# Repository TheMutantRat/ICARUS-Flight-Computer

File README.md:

# ICARUS-Flight-Computer
modular high-power rocketry flight computer

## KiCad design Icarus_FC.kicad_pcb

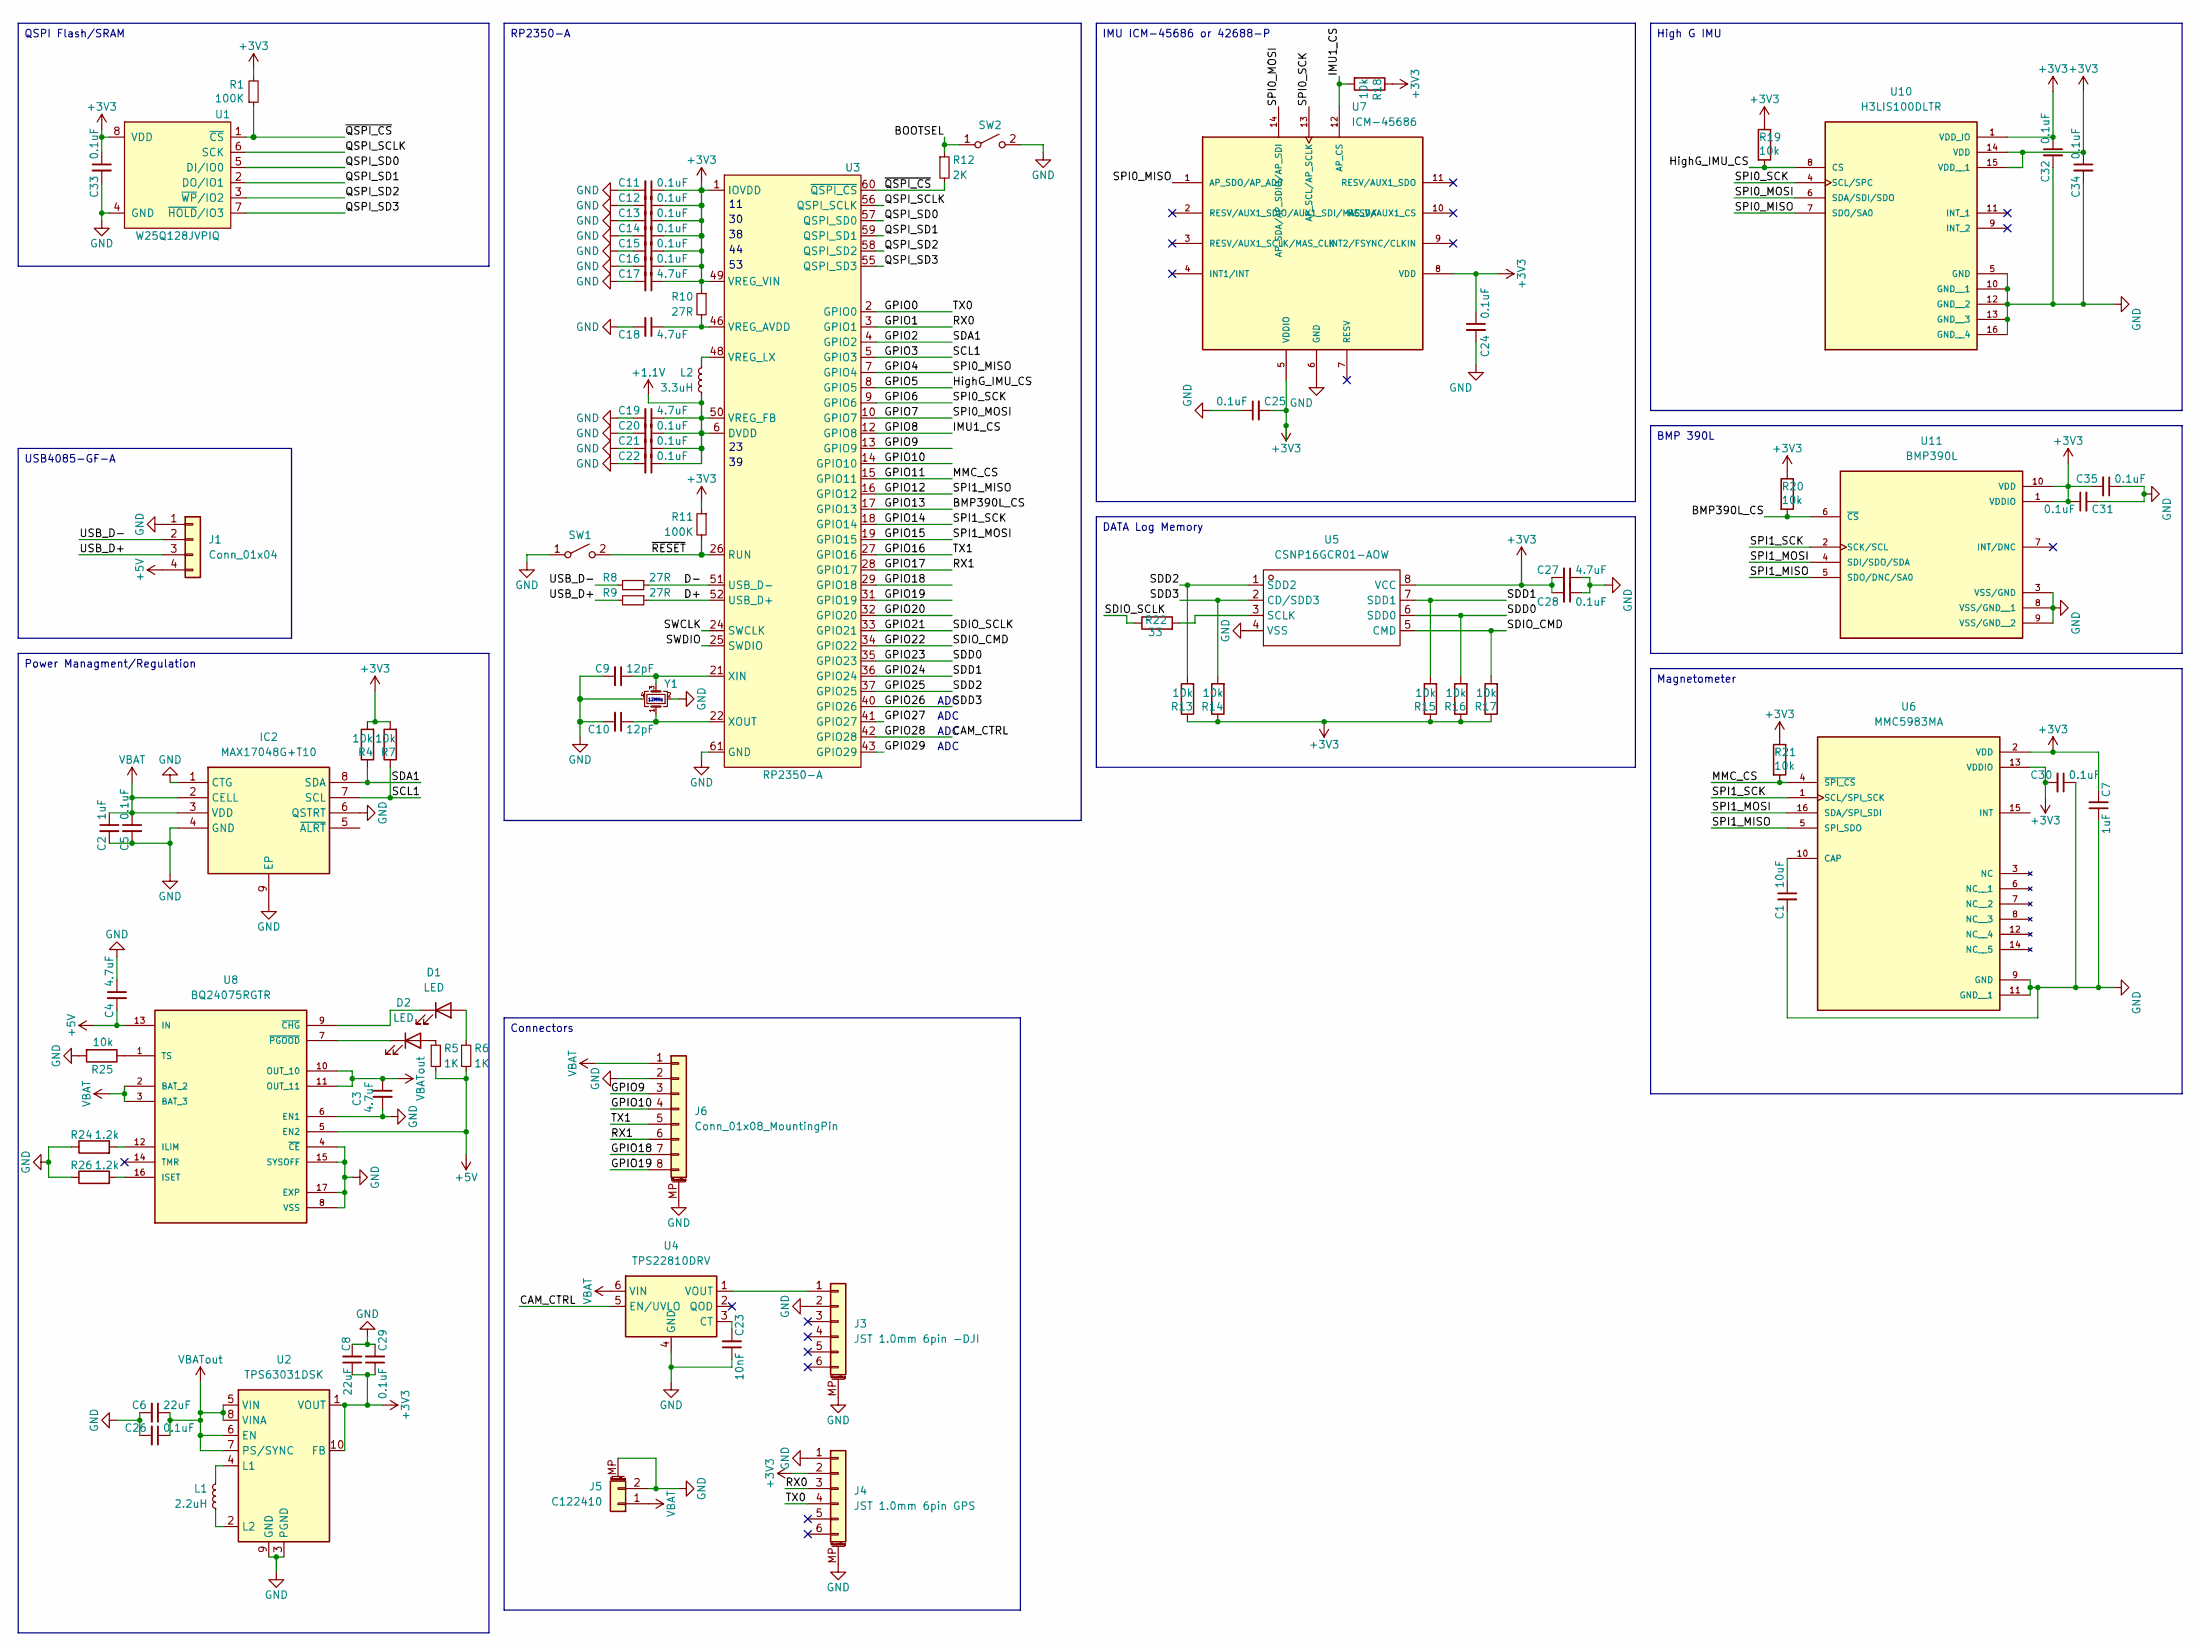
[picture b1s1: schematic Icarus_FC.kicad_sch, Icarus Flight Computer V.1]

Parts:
C1: 10uF; C_0402_1005Metric
C2, C7: 1uF; C_0201_0603Metric
C3, C4, C17, C18, C19, C27: 4.7uF; C_0201_0603Metric
C5, C11, C12, C13, C14, C15, C16, C20, C21, C22, C24, C25, C26, C28, C29, C30, C31, C32, C33, C34, C35: 0.1uF; C_0201_0603Metric
C6, C8: 22uF; C_0402_1005Metric
C9, C10: 12pF; C_0201_0603Metric
C23: 10nF; C_0201_0603Metric
D1, D2: LED; LED_0201_0603Metric
IC2: MAX17048G+T10; SON50P200X200X80-9N-D; Mouser Part Number 700-MAX17048G+T10
J1: Conn_01x04; JST_SH_SM04B-SRSS-TB_1x04-1MP_P1.00mm_Horizontal
J3: JST 1.0mm 6pin -DJI; JST_SH_SM06B-SRSS-TB_1x06-1MP_P1.00mm_Horizontal
J4: JST 1.0mm 6pin GPS; JST_SH_SM06B-SRSS-TB_1x06-1MP_P1.00mm_Horizontal
J5: C122410; Molex_PicoBlade_53398-0271_1x02-1MP_P1.25mm_Vertical
J6: Conn_01x08_MountingPin; JST_SH_SM08B-SRSS-TB_1x08-1MP_P1.00mm_Horizontal
L1: 2.2uH; ASMPM-0806; LCSC C17701149
L2: 3.3uH; ASMPM-0806; LCSC C42411119
R1, R11: 100K; R_0201_0603Metric
R4, R7, R13, R14, R15, R16, R17, R18, R19, R20, R21, R25: 10k; R_0201_0603Metric
R5, R6: 1K; R_0201_0603Metric
R8, R9, R10: 27R; R_0201_0603Metric
R12: 2K; R_0201_0603Metric
R22: 33; R_0201_0603Metric
R24, R26: 1.2k; R_0201_0603Metric
SW1: SW_BOOTSEL; KEY-SMD_B3U-3000P; LCSC C963349
SW2: SW_RESET; KEY-SMD_B3U-3000P; LCSC C963349
U1: W25Q128JVPIQ; WSON-8-1EP_6x5mm_P1.27mm_EP3.4x4mm; LCSC C190862
U2: TPS63031DSK; WSON-10-1EP_2.5x2.5mm_P0.5mm_EP1.2x2mm_ThermalVias
U3: RP2350-A; QFN-60-1EP_7x7mm_P0.4mm_EP3.4x3.4mm_ThermalVias
U4: TPS22810DRV; WSON-6-1EP_2x2mm_P0.65mm_EP1x1.6mm
U5: CSNP16GCR01-AOW; LGA-8_8x6.2mm_P1.27mm; Manufacturer Part CSNP16GCR01-AOW; LCSC Part Name CS Gen2 SDNAND 16Gb pSLC LongP/ECycle 工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
U6: MMC5983MA; PQFN50P300X300X100-16N; PARTREV A
U7: ICM-45686; IC_ICM-45686; PARTREV 0.2
U8: BQ24075RGTR; QFN50P300X300X100-17N; PARTREV M
U10: H3LIS100DLTR; PQFN50P300X300X100-16N; PARTREV 2
U11: BMP390L; 10LGA_2X2X0p75_BOS; PARTREV 1.7
Y1: CM4012M00012001; Crystal_SMD_2520-4Pin_2.5x2.0mm; LCSC C7294611

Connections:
+1.1V: C19.1, C20.1, C21.1, C22.1, L2.1, U3.6 (DVDD), U3.23 (DVDD), U3.39 (DVDD), U3.50 (VREG_FB)
+3V3: C7.2, C8.1, C11.1, C12.1, C13.1, C14.1, C15.1, C16.1, C17.1, C24.1, C25.2, C27.2, C28.2, C29.1, C30.2, C31.1, C32.1, C33.1, C34.1, C35.2, J4.2, R1.2, R4.2, R7.2, R10.1, R11.1, R13.1, R14.1, R15.1, R16.1, R17.1, R18.1, R19.1, R20.1, R21.1, U1.8 (VDD), U2.1 (VOUT), U2.10 (FB), U3.1 (IOVDD), U3.11 (IOVDD), U3.20 (IOVDD), U3.30 (IOVDD), U3.38 (IOVDD), U3.44 (IOVDD), U3.45 (IOVDD), U3.49 (VREG_VIN), U3.53 (IOVDD), U3.54 (IOVDD), U5.8 (VCC), U6.2 (VDD), U6.13 (VDDIO), U7.5 (VDDIO), U7.8 (VDD), U10.1 (VDD_IO), U10.14 (VDD), U10.15 (VDD__1), U11.1 (VDDIO), U11.10 (VDD)
+5V: C4.2, J1.4, R5.2, R6.2, U8.5 (EN2), U8.13 (IN)
/BMP390L_CS: R20.2, U3.17 (GPIO13), U11.6 (~CS)
/BOOTSEL: R12.1, SW2.1 (A)
/CAM_CTRL: U3.42 (GPIO28), U4.5 (EN/UVLO)
/D+: R9.1, U3.52 (USB_D+)
/D-: R8.1, U3.51 (USB_D-)
/GPIO0: J4.4, U3.2 (GPIO0)
/GPIO1: J4.3, U3.3 (GPIO1)
/GPIO2: IC2.8 (SDA), R4.1, U3.4 (GPIO2)
/GPIO3: IC2.7 (SCL), R7.1, U3.5 (GPIO3)
/GPIO4: U3.7 (GPIO4), U7.1 (AP_SDO/AP_AD0), U10.7 (SDO/SA0)
/GPIO5: R19.2, U3.8 (GPIO5), U10.8 (CS)
/GPIO6: U3.9 (GPIO6), U7.13 (AP_SCL/AP_SCLK), U10.4 (SCL/SPC)
/GPIO7: U3.10 (GPIO7), U7.14 (AP_SDA/AP_SDIO/AP_SDI), U10.6 (SDA/SDI/SDO)
/GPIO8: R18.2, U3.12 (GPIO8), U7.12 (AP_CS)
/GPIO9: J6.3, U3.13 (GPIO9)
/GPIO10: J6.4, U3.14 (GPIO10)
/GPIO11: R21.2, U3.15 (GPIO11), U6.4 (~SPI_CS)
/GPIO12: U3.16 (GPIO12), U6.5 (SPI_SDO), U11.5 (SDO/DNC/SA0)
/GPIO14: U3.18 (GPIO14), U6.1 (SCL/SPI_SCK), U11.2 (SCK/SCL)
/GPIO15: U3.19 (GPIO15), U6.16 (SDA/SPI_SDI), U11.4 (SDI/SDO/SDA)
/GPIO16: J6.5, U3.27 (GPIO16)
/GPIO17: J6.6, U3.28 (GPIO17)
/GPIO18: J6.7, U3.29 (GPIO18)
/GPIO19: J6.8, U3.31 (GPIO19)
/GPIO20: U3.32 (GPIO20)
/GPIO21: R22.1, U3.33 (GPIO21)
/GPIO22: R17.2, U3.34 (GPIO22), U5.5 (CMD)
/GPIO23: R16.2, U3.35 (GPIO23), U5.6 (SDD0)
/GPIO24: R15.2, U3.36 (GPIO24), U5.7 (SDD1)
/GPIO25: R13.2, U3.37 (GPIO25), U5.1 (SDD2)
/GPIO26: R14.2, U3.40 (GPIO26), U5.2 (CD/SDD3)
/GPIO27: U3.41 (GPIO27)
/GPIO29: U3.43 (GPIO29)
/QSPI_SCLK: U1.6 (SCK), U3.56 (QSPI_SCLK)
/QSPI_SD0: U1.5 (DI/IO0), U3.57 (QSPI_SD0)
/QSPI_SD1: U1.2 (DO/IO1), U3.59 (QSPI_SD1)
/QSPI_SD2: U1.3 (~WP/IO2), U3.58 (QSPI_SD2)
/QSPI_SD3: U1.7 (~HOLD/IO3), U3.55 (QSPI_SD3)
/SWCLK: U3.24 (SWCLK)
/SWDIO: U3.25 (SWDIO)
/USB_D+: J1.3, R9.2
/USB_D-: J1.2, R8.2
/~QSPI_CS: R1.1, R12.2, U1.1 (~CS), U3.60 (~QSPI_CS)
/~RESET: R11.2, SW1.2 (B), U3.26 (RUN)
GND: C1.2, C2.2, C3.2, C4.1, C5.2, C6.2, C7.1, C8.2, C9.2, C10.2, C11.2, C12.2, C13.2, C14.2, C15.2, C16.2, C17.2, C18.2, C19.2, C20.2, C21.2, C22.2, C23.1, C24.2, C25.1, C26.2, C27.1, C28.1, C29.2, C30.1, C31.2, C32.2, C33.2, C34.2, C35.1, IC2.1 (CTG), IC2.4 (GND), IC2.6 (QSTRT), IC2.9 (EP), J1.1, J3.2, J3.MP (MountPin), J4.1, J4.MP (MountPin), J5.2, J5.MP (MountPin), J6.2, J6.MP (MountPin), R24.1, R25.2, R26.1, SW1.1 (A), SW2.2 (B), U1.4 (GND), U1.9 (GND), U2.3 (PGND), U2.9 (GND), U2.11 (PGND), U3.47 (GND), U3.61 (GND), U4.4 (GND), U4.7 (GND), U5.4 (VSS), U6.9 (GND), U6.11 (GND__1), U7.6 (GND), U8.4 (~CE), U8.6 (EN1), U8.8 (VSS), U8.15 (SYSOFF), U8.17 (EXP), U10.5 (GND), U10.10 (GND__1), U10.12 (GND__2), U10.13 (GND__3), U10.16 (GND__4), U11.3 (VSS/GND), U11.8 (VSS/GND__1), U11.9 (VSS/GND__2), Y1.2, Y1.4; also elsewhere on the board
unnamed: D1.2 (A), R6.1
unnamed: D1.1 (K), U8.9 (~CHG)
unnamed: D2.2 (A), R5.1
unnamed: D2.1 (K), U8.7 (~PGOOD)
unnamed: J3.1, U4.1 (VOUT)
unnamed: L1.2, U2.4 (L1)
unnamed: L1.1, U2.2 (L2)
unnamed: C18.1, R10.2, U3.46 (VREG_AVDD)
unnamed: L2.2, U3.48 (VREG_LX)
unnamed: C9.1, U3.21 (XIN), Y1.3
unnamed: C10.1, U3.22 (XOUT), Y1.1
unnamed: C23.2, U4.3 (CT)
unnamed: R22.2, U5.3 (SCLK)
unnamed: C1.1, U6.10 (CAP)
unnamed: R24.2, U8.12 (ILIM)
unnamed: R26.2, U8.16 (ISET)
unnamed: R25.1, U8.1 (TS)
VBAT: C2.1, C5.1, IC2.2 (CELL), IC2.3 (VDD), J5.1, J6.1, U4.6 (VIN), U8.2 (BAT_2), U8.3 (BAT_3)
VBATout: C3.1, C6.1, C26.1, U2.5 (VIN), U2.6 (EN), U2.7 (PS/SYNC), U2.8 (VINA), U8.10 (OUT_10), U8.11 (OUT_11)

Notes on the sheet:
ADC
12MHz
IMU ICM-45686 or 42688-P
BMP 390L
QSPI Flash/SRAM
High G IMU
Magnetometer
Power Managment/Regulation
USB4085-GF-A
RP2350-A
Connectors
DATA Log Memory

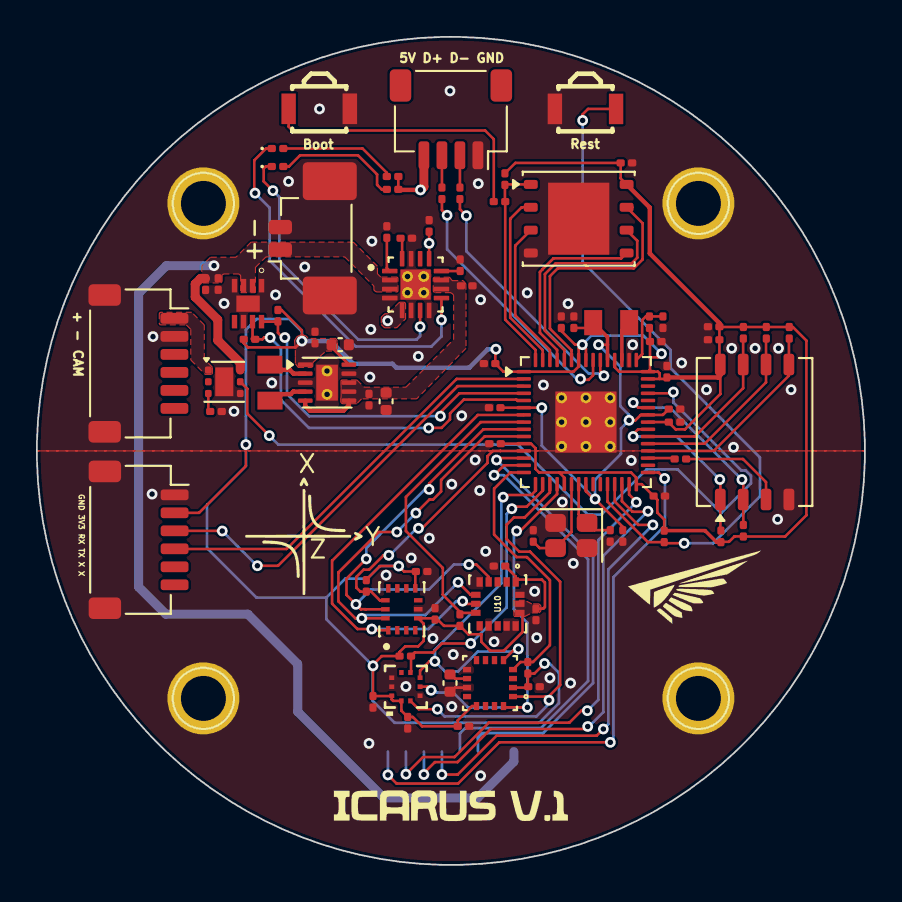
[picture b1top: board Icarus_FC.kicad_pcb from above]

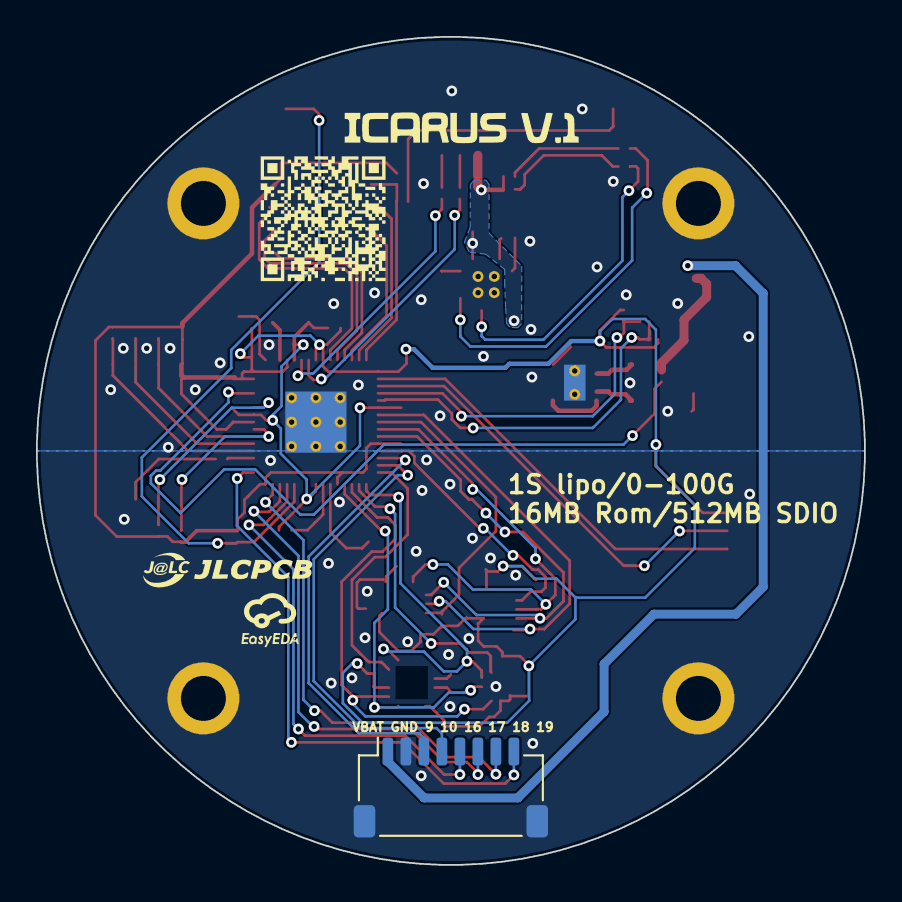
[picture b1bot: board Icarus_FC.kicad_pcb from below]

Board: 4 copper layers, 46.0 x 46.0 mm, 89 parts (3 on the bottom side), 62 nets.

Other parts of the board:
H1, H2, H3, H4: MountingHole; TestPoint_Plated_Hole_D2.0mm
QRCode: LOGO
icon: LOGO
logo: LOGO
logoB: LOGO

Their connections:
GND: H1.1, H2.1, H3.1, H4.1; also elsewhere on the board

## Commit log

2026-02-03 Add screenshot to README.md
